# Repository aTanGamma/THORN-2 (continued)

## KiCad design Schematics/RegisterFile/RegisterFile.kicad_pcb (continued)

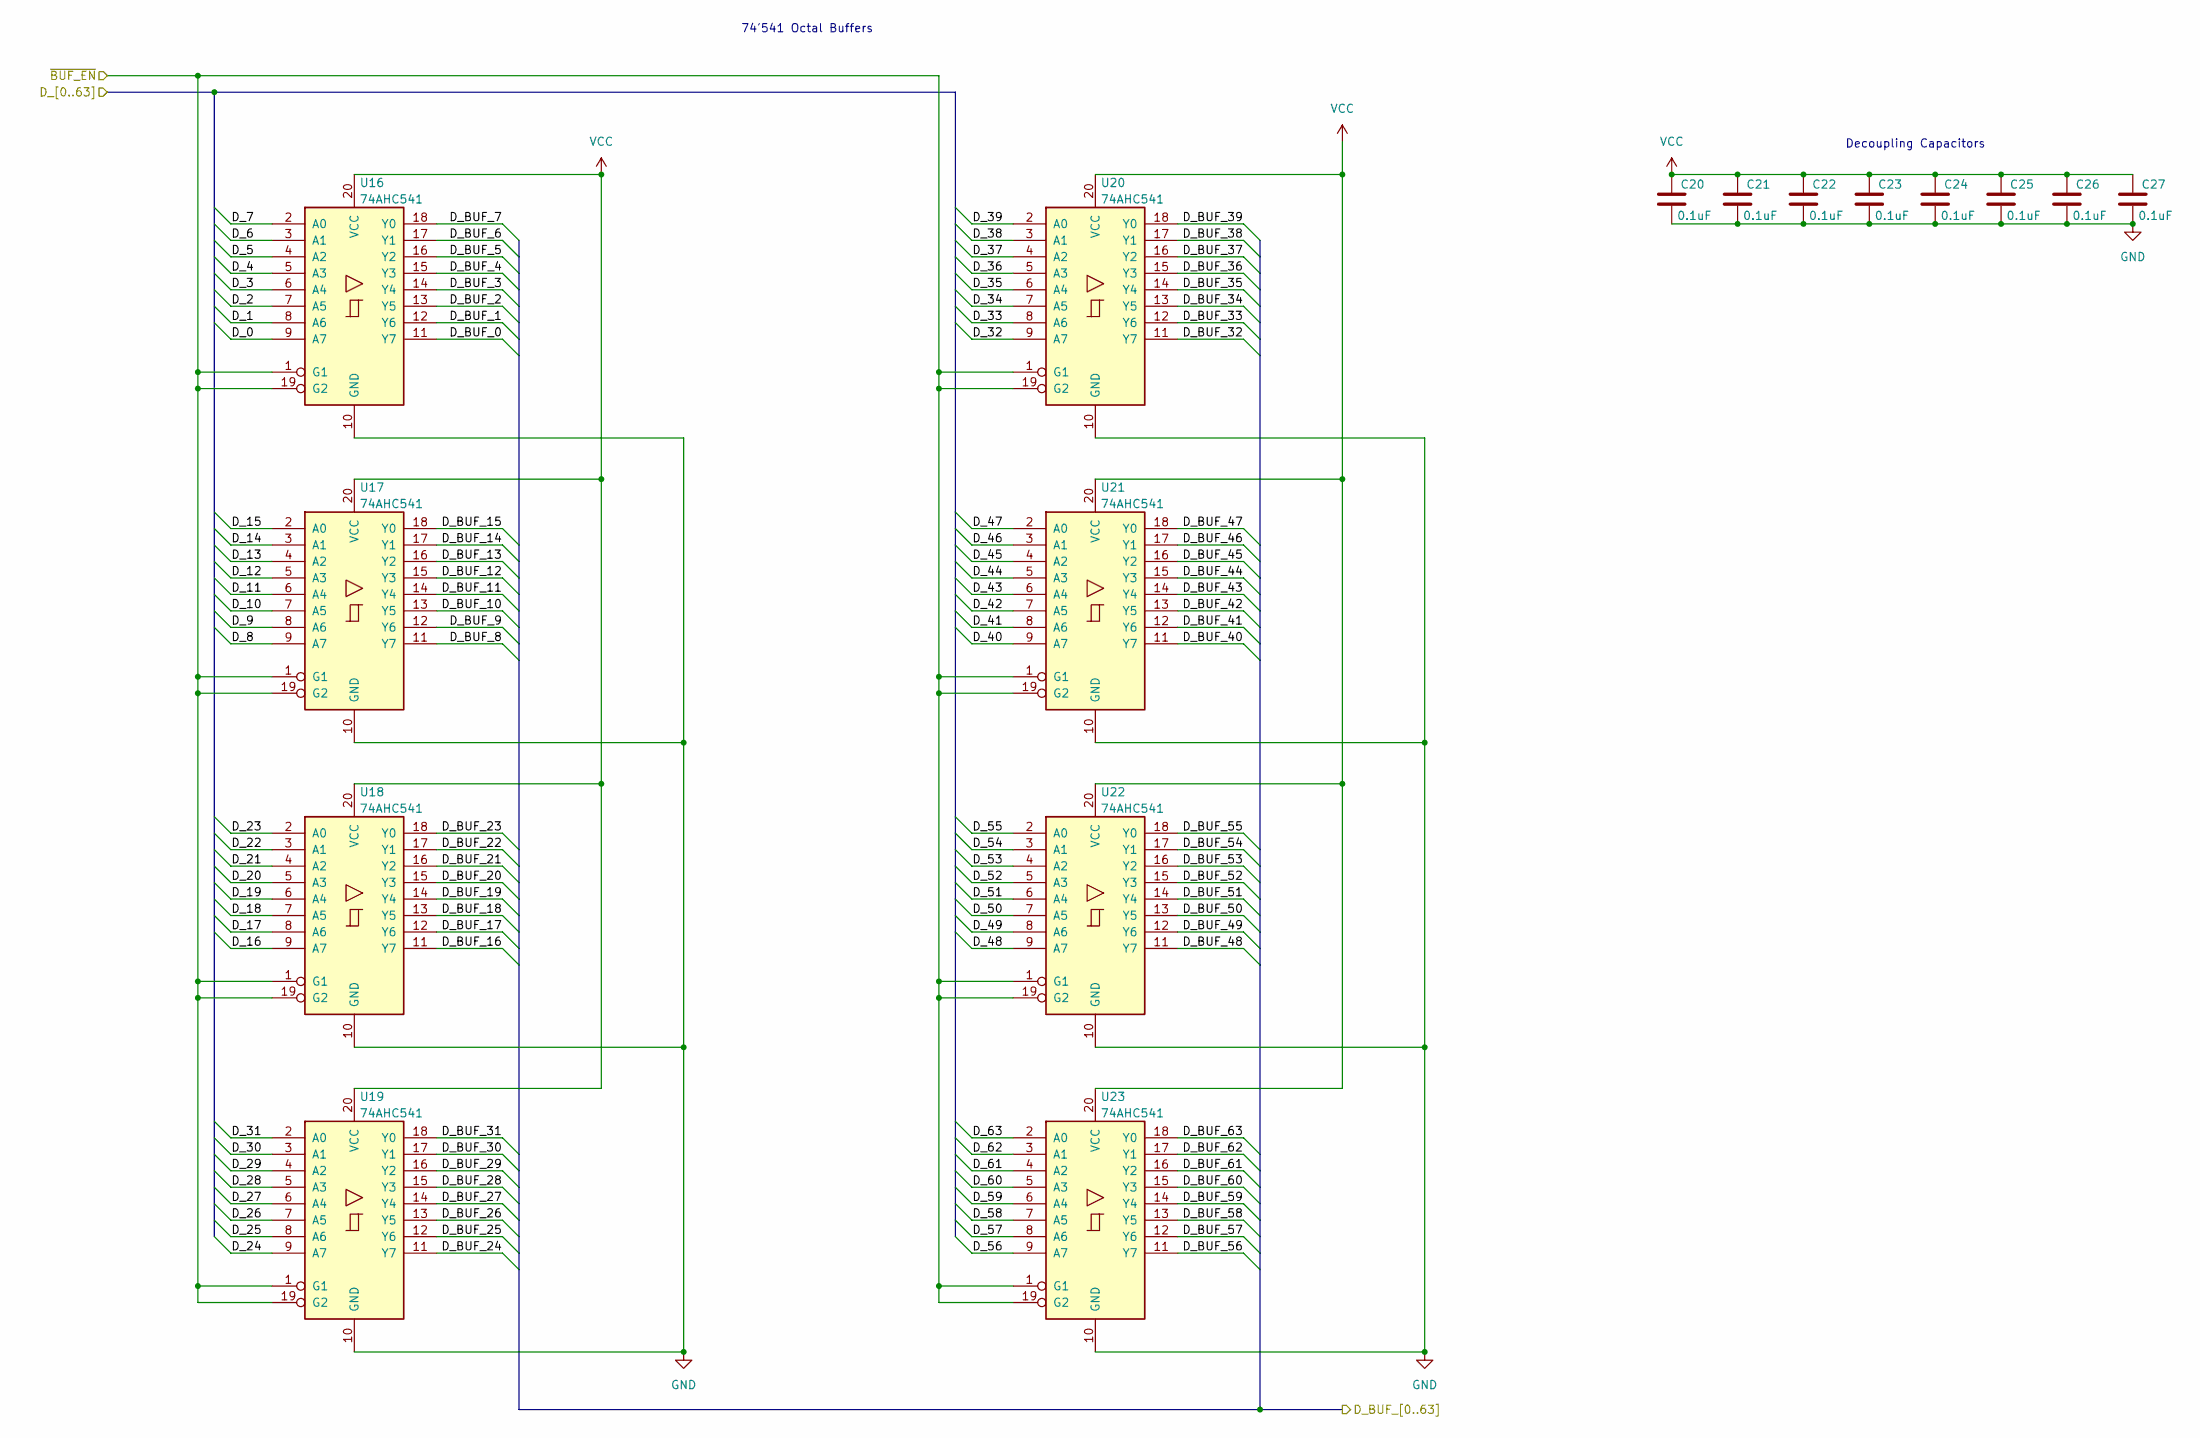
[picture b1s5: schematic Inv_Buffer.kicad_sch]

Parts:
C20, C21, C22, C23, C24, C25, C26, C27: 0.1uF; C_1206_3216Metric
U16, U17, U18, U19, U20, U21, U22, U23: 74AHC541; TSSOP-20_4.4x6.5mm_P0.65mm

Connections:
/REG_OUT_X_0: U16.11 (Y7); also elsewhere on the board
/REG_OUT_X_1: U16.12 (Y6); also elsewhere on the board
/REG_OUT_X_2: U16.13 (Y5); also elsewhere on the board
/REG_OUT_X_3: U16.14 (Y4); also elsewhere on the board
/REG_OUT_X_4: U16.15 (Y3); also elsewhere on the board
/REG_OUT_X_5: U16.16 (Y2); also elsewhere on the board
/REG_OUT_X_6: U16.17 (Y1); also elsewhere on the board
/REG_OUT_X_7: U16.18 (Y0); also elsewhere on the board
/REG_OUT_X_8: U17.11 (Y7); also elsewhere on the board
/REG_OUT_X_9: U17.12 (Y6); also elsewhere on the board
/REG_OUT_X_10: U17.13 (Y5); also elsewhere on the board
/REG_OUT_X_11: U17.14 (Y4); also elsewhere on the board
/REG_OUT_X_12: U17.15 (Y3); also elsewhere on the board
/REG_OUT_X_13: U17.16 (Y2); also elsewhere on the board
/REG_OUT_X_14: U17.17 (Y1); also elsewhere on the board
/REG_OUT_X_15: U17.18 (Y0); also elsewhere on the board
/REG_OUT_X_16: U18.11 (Y7); also elsewhere on the board
/REG_OUT_X_17: U18.12 (Y6); also elsewhere on the board
/REG_OUT_X_18: U18.13 (Y5); also elsewhere on the board
/REG_OUT_X_19: U18.14 (Y4); also elsewhere on the board
/REG_OUT_X_20: U18.15 (Y3); also elsewhere on the board
/REG_OUT_X_21: U18.16 (Y2); also elsewhere on the board
/REG_OUT_X_22: U18.17 (Y1); also elsewhere on the board
/REG_OUT_X_23: U18.18 (Y0); also elsewhere on the board
/REG_OUT_X_24: U19.11 (Y7); also elsewhere on the board
/REG_OUT_X_25: U19.12 (Y6); also elsewhere on the board
/REG_OUT_X_26: U19.13 (Y5); also elsewhere on the board
/REG_OUT_X_27: U19.14 (Y4); also elsewhere on the board
/REG_OUT_X_28: U19.15 (Y3); also elsewhere on the board
/REG_OUT_X_29: U19.16 (Y2); also elsewhere on the board
/REG_OUT_X_30: U19.17 (Y1); also elsewhere on the board
/REG_OUT_X_31: U19.18 (Y0); also elsewhere on the board
/REG_OUT_X_32: U20.11 (Y7); also elsewhere on the board
/REG_OUT_X_33: U20.12 (Y6); also elsewhere on the board
/REG_OUT_X_34: U20.13 (Y5); also elsewhere on the board
/REG_OUT_X_35: U20.14 (Y4); also elsewhere on the board
/REG_OUT_X_36: U20.15 (Y3); also elsewhere on the board
/REG_OUT_X_37: U20.16 (Y2); also elsewhere on the board
/REG_OUT_X_38: U20.17 (Y1); also elsewhere on the board
/REG_OUT_X_39: U20.18 (Y0); also elsewhere on the board
/REG_OUT_X_40: U21.11 (Y7); also elsewhere on the board
/REG_OUT_X_41: U21.12 (Y6); also elsewhere on the board
/REG_OUT_X_42: U21.13 (Y5); also elsewhere on the board
/REG_OUT_X_43: U21.14 (Y4); also elsewhere on the board
/REG_OUT_X_44: U21.15 (Y3); also elsewhere on the board
/REG_OUT_X_45: U21.16 (Y2); also elsewhere on the board
/REG_OUT_X_46: U21.17 (Y1); also elsewhere on the board
/REG_OUT_X_47: U21.18 (Y0); also elsewhere on the board
/REG_OUT_X_48: U22.11 (Y7); also elsewhere on the board
/REG_OUT_X_49: U22.12 (Y6); also elsewhere on the board
/REG_OUT_X_50: U22.13 (Y5); also elsewhere on the board
/REG_OUT_X_51: U22.14 (Y4); also elsewhere on the board
/REG_OUT_X_52: U22.15 (Y3); also elsewhere on the board
/REG_OUT_X_53: U22.16 (Y2); also elsewhere on the board
/REG_OUT_X_54: U22.17 (Y1); also elsewhere on the board
/REG_OUT_X_55: U22.18 (Y0); also elsewhere on the board
/REG_OUT_X_56: U23.11 (Y7); also elsewhere on the board
/REG_OUT_X_57: U23.12 (Y6); also elsewhere on the board
/REG_OUT_X_58: U23.13 (Y5); also elsewhere on the board
/REG_OUT_X_59: U23.14 (Y4); also elsewhere on the board
/REG_OUT_X_60: U23.15 (Y3); also elsewhere on the board
/REG_OUT_X_61: U23.16 (Y2); also elsewhere on the board
/REG_OUT_X_62: U23.17 (Y1); also elsewhere on the board
/REG_OUT_X_63: U23.18 (Y0); also elsewhere on the board
/Register_RAM_Bank X/Data_0: U16.9 (A7); also elsewhere on the board
/Register_RAM_Bank X/Data_1: U16.8 (A6); also elsewhere on the board
/Register_RAM_Bank X/Data_2: U16.7 (A5); also elsewhere on the board
/Register_RAM_Bank X/Data_3: U16.6 (A4); also elsewhere on the board
/Register_RAM_Bank X/Data_4: U16.5 (A3); also elsewhere on the board
/Register_RAM_Bank X/Data_5: U16.4 (A2); also elsewhere on the board
/Register_RAM_Bank X/Data_6: U16.3 (A1); also elsewhere on the board
/Register_RAM_Bank X/Data_7: U16.2 (A0); also elsewhere on the board
/Register_RAM_Bank X/Data_8: U17.9 (A7); also elsewhere on the board
/Register_RAM_Bank X/Data_9: U17.8 (A6); also elsewhere on the board
/Register_RAM_Bank X/Data_10: U17.7 (A5); also elsewhere on the board
/Register_RAM_Bank X/Data_11: U17.6 (A4); also elsewhere on the board
/Register_RAM_Bank X/Data_12: U17.5 (A3); also elsewhere on the board
/Register_RAM_Bank X/Data_13: U17.4 (A2); also elsewhere on the board
/Register_RAM_Bank X/Data_14: U17.3 (A1); also elsewhere on the board
/Register_RAM_Bank X/Data_15: U17.2 (A0); also elsewhere on the board
/Register_RAM_Bank X/Data_16: U18.9 (A7); also elsewhere on the board
/Register_RAM_Bank X/Data_17: U18.8 (A6); also elsewhere on the board
/Register_RAM_Bank X/Data_18: U18.7 (A5); also elsewhere on the board
/Register_RAM_Bank X/Data_19: U18.6 (A4); also elsewhere on the board
/Register_RAM_Bank X/Data_20: U18.5 (A3); also elsewhere on the board
/Register_RAM_Bank X/Data_21: U18.4 (A2); also elsewhere on the board
/Register_RAM_Bank X/Data_22: U18.3 (A1); also elsewhere on the board
/Register_RAM_Bank X/Data_23: U18.2 (A0); also elsewhere on the board
/Register_RAM_Bank X/Data_24: U19.9 (A7); also elsewhere on the board
/Register_RAM_Bank X/Data_25: U19.8 (A6); also elsewhere on the board
/Register_RAM_Bank X/Data_26: U19.7 (A5); also elsewhere on the board
/Register_RAM_Bank X/Data_27: U19.6 (A4); also elsewhere on the board
/Register_RAM_Bank X/Data_28: U19.5 (A3); also elsewhere on the board
/Register_RAM_Bank X/Data_29: U19.4 (A2); also elsewhere on the board
/Register_RAM_Bank X/Data_30: U19.3 (A1); also elsewhere on the board
/Register_RAM_Bank X/Data_31: U19.2 (A0); also elsewhere on the board
/Register_RAM_Bank X/Data_32: U20.9 (A7); also elsewhere on the board
/Register_RAM_Bank X/Data_33: U20.8 (A6); also elsewhere on the board
/Register_RAM_Bank X/Data_34: U20.7 (A5); also elsewhere on the board
/Register_RAM_Bank X/Data_35: U20.6 (A4); also elsewhere on the board
/Register_RAM_Bank X/Data_36: U20.5 (A3); also elsewhere on the board
/Register_RAM_Bank X/Data_37: U20.4 (A2); also elsewhere on the board
/Register_RAM_Bank X/Data_38: U20.3 (A1); also elsewhere on the board
/Register_RAM_Bank X/Data_39: U20.2 (A0); also elsewhere on the board
/Register_RAM_Bank X/Data_40: U21.9 (A7); also elsewhere on the board
/Register_RAM_Bank X/Data_41: U21.8 (A6); also elsewhere on the board
/Register_RAM_Bank X/Data_42: U21.7 (A5); also elsewhere on the board
/Register_RAM_Bank X/Data_43: U21.6 (A4); also elsewhere on the board
/Register_RAM_Bank X/Data_44: U21.5 (A3); also elsewhere on the board
/Register_RAM_Bank X/Data_45: U21.4 (A2); also elsewhere on the board
/Register_RAM_Bank X/Data_46: U21.3 (A1); also elsewhere on the board
/Register_RAM_Bank X/Data_47: U21.2 (A0); also elsewhere on the board
/Register_RAM_Bank X/Data_48: U22.9 (A7); also elsewhere on the board
/Register_RAM_Bank X/Data_49: U22.8 (A6); also elsewhere on the board
/Register_RAM_Bank X/Data_50: U22.7 (A5); also elsewhere on the board
/Register_RAM_Bank X/Data_51: U22.6 (A4); also elsewhere on the board
/Register_RAM_Bank X/Data_52: U22.5 (A3); also elsewhere on the board
/Register_RAM_Bank X/Data_53: U22.4 (A2); also elsewhere on the board
/Register_RAM_Bank X/Data_54: U22.3 (A1); also elsewhere on the board
/Register_RAM_Bank X/Data_55: U22.2 (A0); also elsewhere on the board
/Register_RAM_Bank X/Data_56: U23.9 (A7); also elsewhere on the board
/Register_RAM_Bank X/Data_57: U23.8 (A6); also elsewhere on the board
/Register_RAM_Bank X/Data_58: U23.7 (A5); also elsewhere on the board
/Register_RAM_Bank X/Data_59: U23.6 (A4); also elsewhere on the board
/Register_RAM_Bank X/Data_60: U23.5 (A3); also elsewhere on the board
/Register_RAM_Bank X/Data_61: U23.4 (A2); also elsewhere on the board
/Register_RAM_Bank X/Data_62: U23.3 (A1); also elsewhere on the board
/Register_RAM_Bank X/Data_63: U23.2 (A0); also elsewhere on the board
/~BUF_EN_X: U16.1 (G1), U16.19 (G2), U17.1 (G1), U17.19 (G2), U18.1 (G1), U18.19 (G2), U19.1 (G1), U19.19 (G2), U20.1 (G1), U20.19 (G2), U21.1 (G1), U21.19 (G2), U22.1 (G1), U22.19 (G2), U23.1 (G1), U23.19 (G2); also elsewhere on the board
GND: C20.2, C21.2, C22.2, C23.2, C24.2, C25.2, C26.2, C27.2, U16.10 (GND), U17.10 (GND), U18.10 (GND), U19.10 (GND), U20.10 (GND), U21.10 (GND), U22.10 (GND), U23.10 (GND); also elsewhere on the board
VCC: C20.1, C21.1, C22.1, C23.1, C24.1, C25.1, C26.1, C27.1, U16.20 (VCC), U17.20 (VCC), U18.20 (VCC), U19.20 (VCC), U20.20 (VCC), U21.20 (VCC), U22.20 (VCC), U23.20 (VCC); also elsewhere on the board

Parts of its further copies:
C28, C29, C30, C31, C32, C33, C34, C35: 0.1uF; C_1206_3216Metric
U24, U25, U26, U27, U28, U29, U30, U31: 74AHC541; TSSOP-20_4.4x6.5mm_P0.65mm

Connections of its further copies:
/Register_RAM_Bank X/Data_0: U24.11 (Y7); also elsewhere on the board
/Register_RAM_Bank X/Data_1: U24.12 (Y6); also elsewhere on the board
/Register_RAM_Bank X/Data_2: U24.13 (Y5); also elsewhere on the board
/Register_RAM_Bank X/Data_3: U24.14 (Y4); also elsewhere on the board
/Register_RAM_Bank X/Data_4: U24.15 (Y3); also elsewhere on the board
/Register_RAM_Bank X/Data_5: U24.16 (Y2); also elsewhere on the board
/Register_RAM_Bank X/Data_6: U24.17 (Y1); also elsewhere on the board
/Register_RAM_Bank X/Data_7: U24.18 (Y0); also elsewhere on the board
/Register_RAM_Bank X/Data_8: U25.11 (Y7); also elsewhere on the board
/Register_RAM_Bank X/Data_9: U25.12 (Y6); also elsewhere on the board
/Register_RAM_Bank X/Data_10: U25.13 (Y5); also elsewhere on the board
/Register_RAM_Bank X/Data_11: U25.14 (Y4); also elsewhere on the board
/Register_RAM_Bank X/Data_12: U25.15 (Y3); also elsewhere on the board
/Register_RAM_Bank X/Data_13: U25.16 (Y2); also elsewhere on the board
/Register_RAM_Bank X/Data_14: U25.17 (Y1); also elsewhere on the board
/Register_RAM_Bank X/Data_15: U25.18 (Y0); also elsewhere on the board
/Register_RAM_Bank X/Data_16: U26.11 (Y7); also elsewhere on the board
/Register_RAM_Bank X/Data_17: U26.12 (Y6); also elsewhere on the board
/Register_RAM_Bank X/Data_18: U26.13 (Y5); also elsewhere on the board
/Register_RAM_Bank X/Data_19: U26.14 (Y4); also elsewhere on the board
/Register_RAM_Bank X/Data_20: U26.15 (Y3); also elsewhere on the board
/Register_RAM_Bank X/Data_21: U26.16 (Y2); also elsewhere on the board
/Register_RAM_Bank X/Data_22: U26.17 (Y1); also elsewhere on the board
/Register_RAM_Bank X/Data_23: U26.18 (Y0); also elsewhere on the board
/Register_RAM_Bank X/Data_24: U27.11 (Y7); also elsewhere on the board
/Register_RAM_Bank X/Data_25: U27.12 (Y6); also elsewhere on the board
/Register_RAM_Bank X/Data_26: U27.13 (Y5); also elsewhere on the board
/Register_RAM_Bank X/Data_27: U27.14 (Y4); also elsewhere on the board
/Register_RAM_Bank X/Data_28: U27.15 (Y3); also elsewhere on the board
/Register_RAM_Bank X/Data_29: U27.16 (Y2); also elsewhere on the board
/Register_RAM_Bank X/Data_30: U27.17 (Y1); also elsewhere on the board
/Register_RAM_Bank X/Data_31: U27.18 (Y0); also elsewhere on the board
/Register_RAM_Bank X/Data_32: U28.11 (Y7); also elsewhere on the board
/Register_RAM_Bank X/Data_33: U28.12 (Y6); also elsewhere on the board
/Register_RAM_Bank X/Data_34: U28.13 (Y5); also elsewhere on the board
/Register_RAM_Bank X/Data_35: U28.14 (Y4); also elsewhere on the board
/Register_RAM_Bank X/Data_36: U28.15 (Y3); also elsewhere on the board
/Register_RAM_Bank X/Data_37: U28.16 (Y2); also elsewhere on the board
/Register_RAM_Bank X/Data_38: U28.17 (Y1); also elsewhere on the board
/Register_RAM_Bank X/Data_39: U28.18 (Y0); also elsewhere on the board
/Register_RAM_Bank X/Data_40: U29.11 (Y7); also elsewhere on the board
/Register_RAM_Bank X/Data_41: U29.12 (Y6); also elsewhere on the board
/Register_RAM_Bank X/Data_42: U29.13 (Y5); also elsewhere on the board
/Register_RAM_Bank X/Data_43: U29.14 (Y4); also elsewhere on the board
/Register_RAM_Bank X/Data_44: U29.15 (Y3); also elsewhere on the board
/Register_RAM_Bank X/Data_45: U29.16 (Y2); also elsewhere on the board
/Register_RAM_Bank X/Data_46: U29.17 (Y1); also elsewhere on the board
/Register_RAM_Bank X/Data_47: U29.18 (Y0); also elsewhere on the board
/Register_RAM_Bank X/Data_48: U30.11 (Y7); also elsewhere on the board
/Register_RAM_Bank X/Data_49: U30.12 (Y6); also elsewhere on the board
/Register_RAM_Bank X/Data_50: U30.13 (Y5); also elsewhere on the board
/Register_RAM_Bank X/Data_51: U30.14 (Y4); also elsewhere on the board
/Register_RAM_Bank X/Data_52: U30.15 (Y3); also elsewhere on the board
/Register_RAM_Bank X/Data_53: U30.16 (Y2); also elsewhere on the board
/Register_RAM_Bank X/Data_54: U30.17 (Y1); also elsewhere on the board
/Register_RAM_Bank X/Data_55: U30.18 (Y0); also elsewhere on the board
/Register_RAM_Bank X/Data_56: U31.11 (Y7); also elsewhere on the board
/Register_RAM_Bank X/Data_57: U31.12 (Y6); also elsewhere on the board
/Register_RAM_Bank X/Data_58: U31.13 (Y5); also elsewhere on the board
/Register_RAM_Bank X/Data_59: U31.14 (Y4); also elsewhere on the board
/Register_RAM_Bank X/Data_60: U31.15 (Y3); also elsewhere on the board
/Register_RAM_Bank X/Data_61: U31.16 (Y2); also elsewhere on the board
/Register_RAM_Bank X/Data_62: U31.17 (Y1); also elsewhere on the board
/Register_RAM_Bank X/Data_63: U31.18 (Y0); also elsewhere on the board
/WB_DATA_0: U24.9 (A7); also elsewhere on the board
/WB_DATA_1: U24.8 (A6); also elsewhere on the board
/WB_DATA_2: U24.7 (A5); also elsewhere on the board
/WB_DATA_3: U24.6 (A4); also elsewhere on the board
/WB_DATA_4: U24.5 (A3); also elsewhere on the board
/WB_DATA_5: U24.4 (A2); also elsewhere on the board
/WB_DATA_6: U24.3 (A1); also elsewhere on the board
/WB_DATA_7: U24.2 (A0); also elsewhere on the board
/WB_DATA_8: U25.9 (A7); also elsewhere on the board
/WB_DATA_9: U25.8 (A6); also elsewhere on the board
/WB_DATA_10: U25.7 (A5); also elsewhere on the board
/WB_DATA_11: U25.6 (A4); also elsewhere on the board
/WB_DATA_12: U25.5 (A3); also elsewhere on the board
/WB_DATA_13: U25.4 (A2); also elsewhere on the board
/WB_DATA_14: U25.3 (A1); also elsewhere on the board
/WB_DATA_15: U25.2 (A0); also elsewhere on the board
/WB_DATA_16: U26.9 (A7); also elsewhere on the board
/WB_DATA_17: U26.8 (A6); also elsewhere on the board
/WB_DATA_18: U26.7 (A5); also elsewhere on the board
/WB_DATA_19: U26.6 (A4); also elsewhere on the board
/WB_DATA_20: U26.5 (A3); also elsewhere on the board
/WB_DATA_21: U26.4 (A2); also elsewhere on the board
/WB_DATA_22: U26.3 (A1); also elsewhere on the board
/WB_DATA_23: U26.2 (A0); also elsewhere on the board
/WB_DATA_24: U27.9 (A7); also elsewhere on the board
/WB_DATA_25: U27.8 (A6); also elsewhere on the board
/WB_DATA_26: U27.7 (A5); also elsewhere on the board
/WB_DATA_27: U27.6 (A4); also elsewhere on the board
/WB_DATA_28: U27.5 (A3); also elsewhere on the board
/WB_DATA_29: U27.4 (A2); also elsewhere on the board
/WB_DATA_30: U27.3 (A1); also elsewhere on the board
/WB_DATA_31: U27.2 (A0); also elsewhere on the board
/WB_DATA_32: U28.9 (A7); also elsewhere on the board
/WB_DATA_33: U28.8 (A6); also elsewhere on the board
/WB_DATA_34: U28.7 (A5); also elsewhere on the board
/WB_DATA_35: U28.6 (A4); also elsewhere on the board
/WB_DATA_36: U28.5 (A3); also elsewhere on the board
/WB_DATA_37: U28.4 (A2); also elsewhere on the board
/WB_DATA_38: U28.3 (A1); also elsewhere on the board
/WB_DATA_39: U28.2 (A0); also elsewhere on the board
/WB_DATA_40: U29.9 (A7); also elsewhere on the board
/WB_DATA_41: U29.8 (A6); also elsewhere on the board
/WB_DATA_42: U29.7 (A5); also elsewhere on the board
/WB_DATA_43: U29.6 (A4); also elsewhere on the board
/WB_DATA_44: U29.5 (A3); also elsewhere on the board
/WB_DATA_45: U29.4 (A2); also elsewhere on the board
/WB_DATA_46: U29.3 (A1); also elsewhere on the board
/WB_DATA_47: U29.2 (A0); also elsewhere on the board
/WB_DATA_48: U30.9 (A7); also elsewhere on the board
/WB_DATA_49: U30.8 (A6); also elsewhere on the board
/WB_DATA_50: U30.7 (A5); also elsewhere on the board
/WB_DATA_51: U30.6 (A4); also elsewhere on the board
/WB_DATA_52: U30.5 (A3); also elsewhere on the board
/WB_DATA_53: U30.4 (A2); also elsewhere on the board
/WB_DATA_54: U30.3 (A1); also elsewhere on the board
/WB_DATA_55: U30.2 (A0); also elsewhere on the board
/WB_DATA_56: U31.9 (A7); also elsewhere on the board
/WB_DATA_57: U31.8 (A6); also elsewhere on the board
/WB_DATA_58: U31.7 (A5); also elsewhere on the board
/WB_DATA_59: U31.6 (A4); also elsewhere on the board
/WB_DATA_60: U31.5 (A3); also elsewhere on the board
/WB_DATA_61: U31.4 (A2); also elsewhere on the board
/WB_DATA_62: U31.3 (A1); also elsewhere on the board
/WB_DATA_63: U31.2 (A0); also elsewhere on the board
/~WE: U24.1 (G1), U24.19 (G2), U25.1 (G1), U25.19 (G2), U26.1 (G1), U26.19 (G2), U27.1 (G1), U27.19 (G2), U28.1 (G1), U28.19 (G2), U29.1 (G1), U29.19 (G2), U30.1 (G1), U30.19 (G2), U31.1 (G1), U31.19 (G2); also elsewhere on the board
GND: C28.2, C29.2, C30.2, C31.2, C32.2, C33.2, C34.2, C35.2, U24.10 (GND), U25.10 (GND), U26.10 (GND), U27.10 (GND), U28.10 (GND), U29.10 (GND), U30.10 (GND), U31.10 (GND); also elsewhere on the board
VCC: C28.1, C29.1, C30.1, C31.1, C32.1, C33.1, C34.1, C35.1, U24.20 (VCC), U25.20 (VCC), U26.20 (VCC), U27.20 (VCC), U28.20 (VCC), U29.20 (VCC), U30.20 (VCC), U31.20 (VCC); also elsewhere on the board

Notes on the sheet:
Decoupling Capacitors
74'541 Octal Buffers

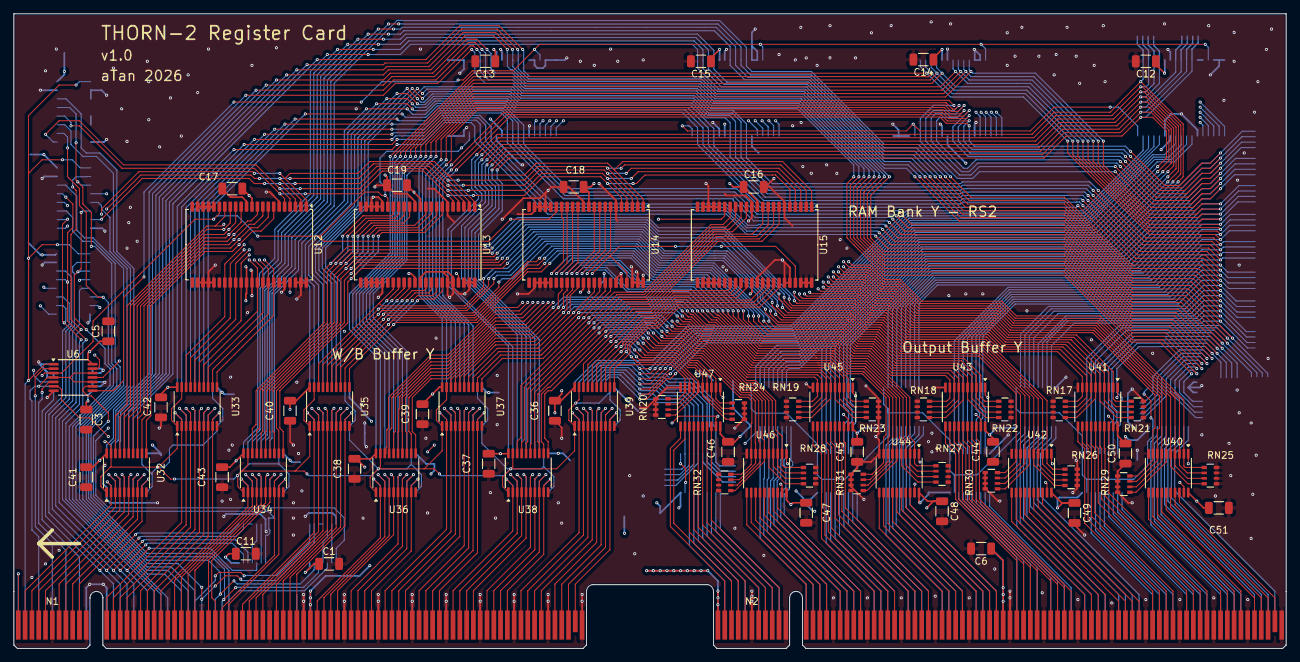
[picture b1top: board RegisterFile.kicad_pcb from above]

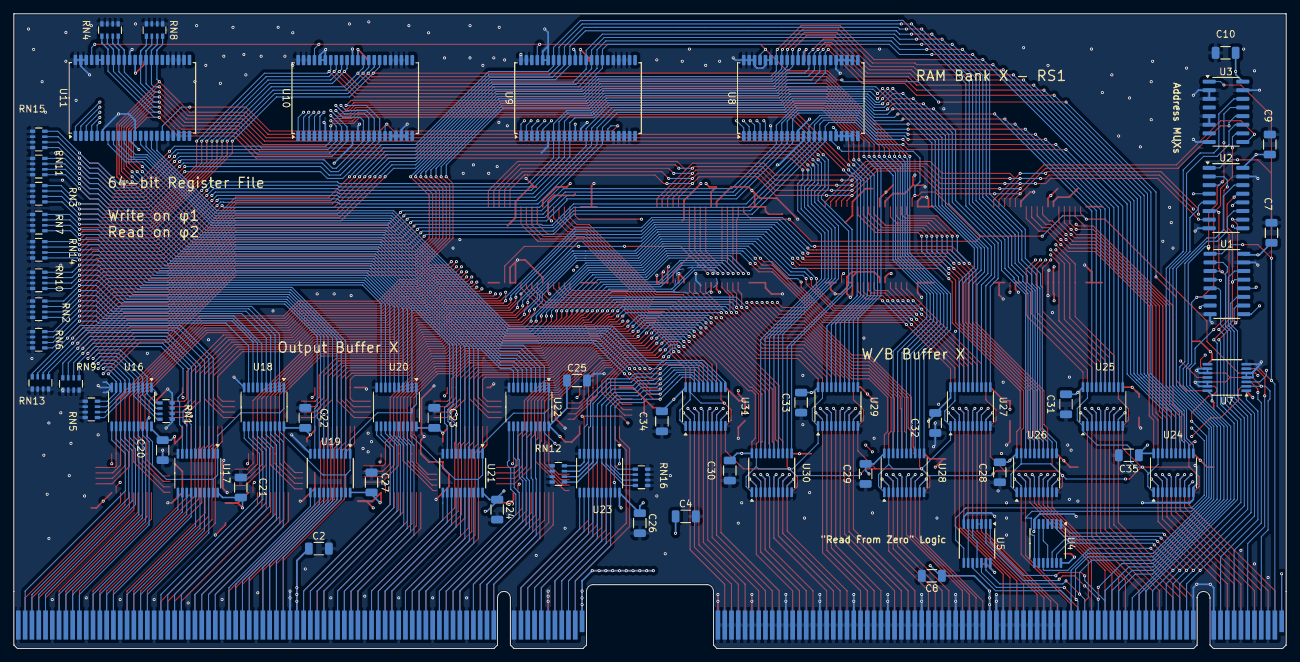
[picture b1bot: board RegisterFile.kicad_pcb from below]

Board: 4 copper layers, 187.3 x 93.5 mm, 132 parts (64 on the bottom side), 365 nets.

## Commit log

2026-04-26 Added README and LICENSE
2026-04-26 Added gitignore
2026-04-26 updated gitignore
2026-04-26 Removed unneeded files
2026-05-23 Updated RegFile diagrams + timing
2026-05-25 Updated Reg section and bits of ALU
2026-06-10 BIG UPDATE: Schematics, PCB & updated writeup for register
2026-06-19 Card Tester PCB made + Register file updates
